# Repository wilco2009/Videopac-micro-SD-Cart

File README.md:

# Videopac µSD cart 
**©2020 Alejandro Valero (Wilco2009)**

Special thanks to Rene Van Den Enden

## INTRODUCTION
The Videopac µSD cart is a revolutionary cartridge allows the loading of Videopac/Magnavox Oddysey2 ROMs from a micro-SD card directly to the console.

Features:
-	Supports the Magnavox Oddysey2, Philips Videopac G7000, Videopac+ G7400, JOPAC and all compatible consoles
-	File selection with OLED display and/or ‘on screen’ game selector
- Supports the following ROM types:
   -	Standard P10/P11 games: 2K, 4K and 8K
   -	XROM games: Game 31 (Musician) & Game 40 (4 In Row)
   -	Videopac+ games: Game 55+ (12K), 58+, 59+ and 60+ (16K)
   -	Soren Gust format: 12K
-	Serial transfer from PC for developers
-	Hexadecimal memory monitor for debugging
-	USB upgradable firmware

## PREREQUISITES
The following items are required for a working system with the Videopac µSD cart:
1.	A Magnavox Oddysey2, Philips Videopac G7000, Videopac+ G7400, JOPAC etc. console
2.	The Videopac µSD cart itself
3.	A micro-SD card (not supplied)
4.	A copy of the “SD.ZIP” file containing the files for the Videopac µSD cart
 
## LAYOUT
The **Videopac µSD cart** connectors and elements are listed below:

## PREPARING THE SD CARD
The **Videopac µSD cart** supports any micro-SD card capacity formatted as FAT16 or FAT32.

The card must fully support the SPI communication protocol – there is a lot of variance in SD cards so for best results please use ‘known brand’ cards and if one card doesn’t work as expected then try another.

Preparing the SD card for the **Videopac µSD cart** is simple:

-	Card must be formatted in FAT16 or FAT32 format
-	The "GAMELIST.INI" file (see below) must be in the root directory of the card
-	A directory called “SYS” must be in the root directory
-	The master skeleton copy of the on-screen game selector ROM "SELECTGAME.BIN" must be in the “SYS” directory

A ZIP file “SD.ZIP” is supplied with the minimum structure required on the card which can be unzipped directly to the root of a freshly formatted SD card.

**Note:** Do not copy any other "SELECTGAME.BIN" into “SYS” other than the master one supplied.

## COPYING ROM FILES
When copying ROM files onto the Videopac µSD cart be aware that the on-screen game selector cannot currently navigate directories. Directories can be used for holding ROM files but will need to be selected using the OLED display and buttons before the game selector runs.

It is recommended that you place all ROM files in the root directory of the card for ease of use of the game selector.

**Note:** This restriction does not apply when directly selecting games using the OLED display and buttons.

## GAMELIST.INI
This file is supplied with the Videopac µSD cart and already contains entries for all the known games for the Videopac/Magnavox Odyssey2 platform, but is editable to make changes or add new entries if required.

The file is laid out in typical Windows INI file format where section names in square brackets correspond to the CRC32  value of a game file and beneath them the characteristics of the game.

An example for a complete game would be the following:

>[4EDA4917]
>
>NAME=01 Speedway! / Spin-Out! / Crypto-Logic!

>YEAR=1978
>
>MANUF=North American Philips Consumer Electronics Corp.
>
>VARIANT=Euro
>
>PAGGING=P10/P11

These values are read and used by the OLED display to show which game is running, the value "PAGGING" is used internally by the Videopac µSD cart to know how to manage the game's memory paging mode and can be set for P10/P11, VPPLUS, SOREN or XROM.

## SELECTGAME.BIN
This is the code for the on-screen file selector menu, use the joystick up and down and fire to select the file to load and once loaded, press ”RESET” key on the console to start.

**Note:** You cannot navigate directories at the current time.

Due to the way the console interacts with the **Videopac µSD cart**, a copy of the skeleton selection code from the “SYS” directory must be copied into the current directory and populated with the files it needs to show in this location, this is done when activating the “VPMENU” option.

The menu allows a maximum of 200 files at any one time, if there are more than this then moving left or right with the joystick will select the next group of 200 files.

When changing file group to get the next set of 200 files a new copy of “SELECTGAME.BIN” containing these files must be loaded, this is then activated by pressing the ”RESET” key on the console again.

Once a game is loaded pressing ”RESET” key on the console will restart the game, to return back to the menu, select “VPMENU” on the **Videopac µSD cart** and the menu will reload.

## MAIN MENU

Once the console is started with the **Videopac µSD cart** inserted it will boot and the OLED display will show the main menu options, use Direction buttons/Enter to select:

**OPTIONS:** “LOAD”, “VPMENU”, “CONFIG”, “RECEIVE”, “ABOUT” and “GAME”

### LOAD

This allows the selection of a .BIN file from the contents on the card to load into the **Videopac µSD cart*’s RAM memory using the buttons and the OLED display.
To select the file:

>-	“UP” & “DOWN” go back and forward one file
>-	“LEFT” & “RIGHT” go back and forward 20 files
>-	“ENTER” load the selected file into the memory or enter a sub directory
>-	“ESC” to go to the “FILE” sub-menu

Once the file is loaded into RAM memory with “ENTER”, press the "RESET" key on the console and follow the instructions for the corresponding game.

Pressing the “ESC” button on an item opens the "FILE" sub-menu which will gives access to the following options:

OPTIONS: “INFO”, “MONITOR” and “EXIT”

>-	INFO: Shows the information for the file and the corresponding metadata from “GAMESLIST.INI” if the CRC32 is known
>-	MONITOR: Displays the contents of the RAM memory in hexadecimal

>**Note:** Examining the RAM contents will decouple it from the running host console and will most likely not return without crashing.  When returning from this mode simply press "RESET" on the console to restore the game
>•	EXIT: Return to main menu
 
### VPMENU
Selecting this option will quit the current game and build the on-screen file selector code by making a copy of the skeleton “SELECTGAME.BIN” file in the current directory (as defined in the “LOAD” menu using the buttons and the OLED display) and populating it with the filenames from the current directory. Press the “RESET” button on the console to show the selection menu.

### CONFIG
OPTIONS: “SETDIR”, “AUTLOAD”, “LOGO”, “REBUILD”, “BAUD”, SORTED”
-	SETDIR: Assign the current directory as the directory from where the “SELECTGAME.BIN” will be read if “AUTOLOAD” is set (usually the root)
-	AUTOLOAD: Enables / disables automatic loading of the “SELECTGAME.BIN” file at start-up from the location defined by “SETDIR”
-	LOGO: Activates / deactivates the logo display during start-up
-	REBUILD: The "GAMELIST.INI" file and each directories file information are compiled and cached as binary index files to speed up file access and game information. This means that after changing the "GAMELIST.INI" file or add/removing files the indexes must be rebuilt:
   -	REBUILD GAMELIST: Generates game index file from the “GAMELIST.INI” file 
   -	REBUILD DIRECTORY: Generates file index files of the ROMs contained in the current directory
   -	WHEN: Choose when to perform rebuilding of the file indexes:
       - “ALWAYS”: The directory index is regenerated each time a directory is accessed with no need to regenerate the indexes each time a new ROM is added, but it will take longer to navigate and select a game
       - “MANUALLY”: The directory index files are not regenerated automatically and require manual rebuilding upon changes
- 	BAUD: Allows selection of the transmission speed of the serial port, valid values are: 
   -	9600 bps
   -	19200 bps
   -	38400 bps
   -	57600 bps
   -	115200 bps
-	SORTED: Select “YES” so that the files will appear sorted in alphabetical order
 
### RECEIVE
This is mainly aimed at developers and allows the connection of a PC to the **Videopac µSD cart** through an RS-232 serial connection (such as that supplied by a USB Serial Adaptor or Dongle) to load a program file directly into the RAM of the **Videopac µSD cart**.

The **Videopac µSD cart** serial connector header has the following pinout:

-	3 TX (Connect to the RX pin)
-	2 RX (Connect to the TX pin)
-	1 GND (Connect to the GND pin)

From the **Videopac µSD cart** side, select the desired data transmission speed (“BAUD”) in the “CONFIG” menu and select the “RECEIVE” option, transmission of the file from the PC can then begin.
From the PC side use the “UPLOAD.BAT file”, supplied in the “FLASH&SERIAL.ZIP” file that comes with the **Videopac µSD cart** to transfer the file.
The syntax for “UPLOAD.BAT” file is as follows:

> upload.bat <file.bin> [COMPORT] [BAUDRATE] [PAGGING]
> Where:
> -	COMPORT = COMport
> -	BAUDRATE = 9600, 19200(default), 38400, 56700, 115200
> -	PAGGING = P10/P11, VPPLUS, SOREN, XROM
For example, to load the file "VP01.BIN" at 115200 baud through the COM7 port, select the "RECEIVE" option on the **Videopac µSD cart** and then execute the following command on the PC:
> UPLOAD VP01.BIN COM7 115200 P10/P11
Once completed the transferred program can be executed by pressing “RESET” on the console in the usual way.

### ABOUT
Displays details about the **Videopac µSD cart** and the current version.
 
### GAME
This “easter egg” option allows you to play Videopac games using the OLED Display and direction buttons directly on the **Videopac µSD cart**, firmware V1.04 includes “Race” and “Pong.
To play, remove the **Videopac µSD cart** from the unit and attach the Arduino micro-USB port to a power source to before selecting this option followed by the required game.

When in-game pressing “ESC” will bring up a menu allowing sound to be disabled or the current game to quit and return to start.

To exit game you must remove power from the Arduino micro-USB port.
**Note:** Using the digital direction buttons will result in very different gameplay from using the analogue joysticks – good luck!

## UPDATING THE FIRMWARE
Updating the **Videopac µSD cart** with a new firmware version is as simple as connecting it with a micro-USB cable to a PC and executing a simple command.

Remove the **Videopac µSD cart** from the console and connect the Arduino micro-USB port to the PC, the Arduino driver should install and appear as a new CH340 COM port in the system.

The number of the COM port needs to be known and this can be determined by looking in the "Bluetooth and other devices" window of the Control Panel similar to this:

If there are problems finding the correct number of the port then there is a utility called "LISTCOM.EXE" supplied in the ZIP file that will list all the COM ports available on the PC, test each of these to find the correct port.

Once the port is known proceed to run the flashing utility “VPFLASH.BAT” supplied in the “FLASH&SERIAL.ZIP” ZIP file, having already copied the required ".HEX" firmware file to the same directory as the utility.

Depending on the OLED type on your **Videopac µSD cart** you will need to select the firmware for either the “blue screen” SH1106” or the “white screen” SSD1306.
The syntax of the utility is as follows:

> VPFLASH \[COMPORT\] \<file\>

For example, to load the file "update.HEX" through the COM7 port, execute the following command on the PC:

> VPFLASH COM7 update.HEX

**Note:** DO NOT INTERRUPT THE FLASHING PROCEDURE - Wait for the flashing operation to finish, after which the **Videopac µSD cart** will automatically reset.

## RESTORING FACTORY SETTINGS
To restore the **Videopac µSD cart**’s factory settings, hold both “ENTER”+”ESC” buttons while booting. This option can be used to restore defaults or after installing firmware for the first time.

## BOOTING WITHOUT DISPLAY
If you have any kind of problem with the OLED display it is still possible to use the **Videopac µSD cart** as long as there is a copy of "SELECTGAME.BIN" in the root folder.

By holding the buttons “ESC” + “LEFT” while booting, the **Videopac µSD cart** will automatically go into “VPMENU” mode allowing on-screen game selection with the joystick.

## DIAGNOSTICS
The **Videopac µSD cart** provides a diagnostic utility to output to a serial console in case of any issues.
To access diagnostics, disconnect the **Videopac µSD cart** from the console and connect to a computer with the USB cable from the Arduino micro-USB port.
Open a serial terminal  to the CH340 COM port described above with settings 9600bps, 8bits, no parity, 1 stop bit (9600/8/none/1).
Press “ENTER” + “LEFT” during start-up to access the diagnostic utility via the serial terminal.

## PROGRAMING THE CPLD
Updating the CPLD programming should not normally be required, but it may be necessary to update if a bug is found or some new functionality related to communication with the console is required.
Programming the CPLD requires a XILINX programming cable connected to the JTAG port header of the **Videopac µSD cart**.
It is beyond the scope of this manual to explain updating the CPLD via JTAG, but in the event of a CPLD release further guidance will be given with the update.

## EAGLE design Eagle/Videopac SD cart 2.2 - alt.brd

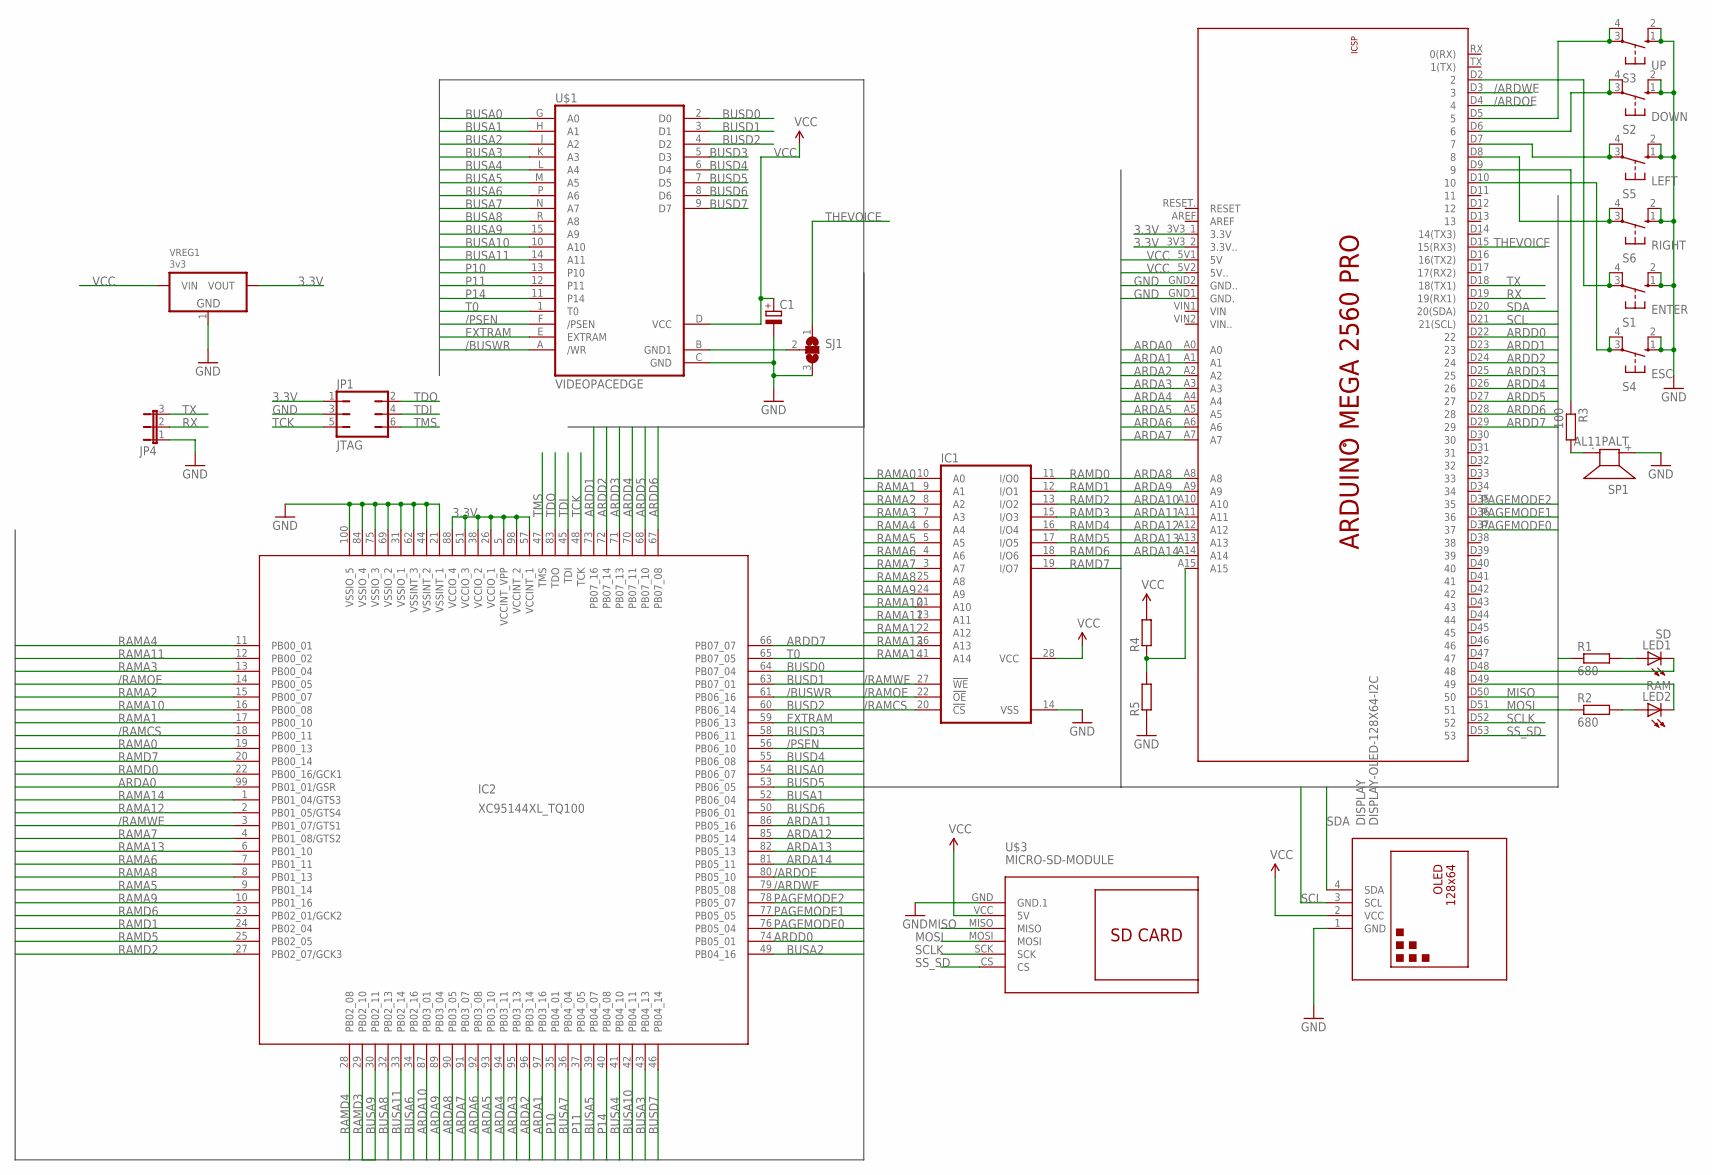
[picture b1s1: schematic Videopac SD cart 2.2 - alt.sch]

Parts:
C1: CPOL-EUE3.5-8; E3,5-8
DISPLAY: DISPLAY-OLED-128X64-I2C
IC1: 62256FPSOP28; SOP28
IC2: XC95144XL_TQ100; XC-TQ100
JP1: JTAG; JP3Q
JP4: JP2E; JP2
LED1: SD; LED3MM
LED2: RAM; LED3MM
R1, R2: 680; 0204/7
R3: 100; 0204/7
R4, R5: R-EU_0204/7; 0204/7
S1: ENTER; B3F-10XX
S2: DOWN; B3F-10XX
S3: UP; B3F-10XX
S4: ESC; B3F-10XX
S5: LEFT; B3F-10XX
S6: RIGHT; B3F-10XX
SJ1: SJ2W; SJ_2
SP1: AL11PALT; ALT
U$1: VIDEOPACEDGE; VIDEOPAC
U$2: ARDUINO_MEGA2560_PRO
U$3: MICRO-SD-MODULE; MICROSD-MODULE
VREG1: 3v3; SOT223

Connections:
3.3V: IC2.5 (VCCINT_VPP), IC2.26 (VCCIO_1), IC2.38 (VCCIO_2), IC2.51 (VCCIO_3), IC2.57 (VCCINT_1), IC2.88 (VCCIO_4), IC2.98 (VCCINT_2), JP1.1, U$2.3V3_1 (3.3V), U$2.3V3_2 (3.3V..), VREG1.2 (VOUT)
/ARDOE: IC2.80 (PB05_10), U$2.D4 (4)
/ARDWE: IC2.79 (PB05_08), U$2.D3 (3)
/BUSWR: IC2.61 (PB06_16), U$1.A (/WR)
/PSEN: IC2.56 (PB06_10), U$1.F (/PSEN)
/RAMCS: IC1.20 (!CS), IC2.18 (PB00_11)
/RAMOE: IC1.22 (!OE), IC2.14 (PB00_05)
/RAMWE: IC1.27 (!WE), IC2.3 (PB01_07/GTS1)
ARDA0: IC2.99 (PB01_01/GSR), U$2.A0
ARDA1: IC2.97 (PB03_16), U$2.A1
ARDA2: IC2.96 (PB03_14), U$2.A2
ARDA3: IC2.95 (PB03_13), U$2.A3
ARDA4: IC2.94 (PB03_11), U$2.A4
ARDA5: IC2.93 (PB03_10), U$2.A5
ARDA6: IC2.92 (PB03_08), U$2.A6
ARDA7: IC2.91 (PB03_07), U$2.A7
ARDA8: IC2.90 (PB03_05), U$2.A8
ARDA9: IC2.89 (PB03_04), U$2.A9
ARDA10: IC2.87 (PB03_01), U$2.A10
ARDA11: IC2.86 (PB05_16), U$2.A11
ARDA12: IC2.85 (PB05_14), U$2.A12
ARDA13: IC2.82 (PB05_13), U$2.A13
ARDA14: IC2.81 (PB05_11), U$2.A14
ARDD0: IC2.74 (PB05_01), U$2.D22 (22)
ARDD1: IC2.73 (PB07_16), U$2.D23 (23)
ARDD2: IC2.72 (PB07_14), U$2.D24 (24)
ARDD3: IC2.71 (PB07_13), U$2.D25 (25)
ARDD4: IC2.70 (PB07_11), U$2.D26 (26)
ARDD5: IC2.68 (PB07_10), U$2.D27 (27)
ARDD6: IC2.67 (PB07_08), U$2.D28 (28)
ARDD7: IC2.66 (PB07_07), U$2.D29 (29)
BUSA0: IC2.54 (PB06_07), U$1.G (A0)
BUSA1: IC2.52 (PB06_04), U$1.H (A1)
BUSA2: IC2.49 (PB04_16), U$1.J (A2)
BUSA3: IC2.43 (PB04_13), U$1.K (A3)
BUSA4: IC2.41 (PB04_10), U$1.L (A4)
BUSA5: IC2.39 (PB04_07), U$1.M (A5)
BUSA6: IC2.34 (PB02_16), U$1.P (A6)
BUSA7: IC2.36 (PB04_04), U$1.N (A7)
BUSA8: IC2.32 (PB02_13), U$1.R (A8)
BUSA9: IC2.30 (PB02_11), U$1.15 (A9)
BUSA10: IC2.42 (PB04_11), U$1.10 (A10)
BUSA11: IC2.33 (PB02_14), U$1.14 (A11)
BUSD0: IC2.64 (PB07_04), U$1.2 (D0)
BUSD1: IC2.63 (PB07_01), U$1.3 (D1)
BUSD2: IC2.60 (PB06_14), U$1.4 (D2)
BUSD3: IC2.58 (PB06_11), U$1.5 (D3)
BUSD4: IC2.55 (PB06_08), U$1.6 (D4)
BUSD5: IC2.53 (PB06_05), U$1.7 (D5)
BUSD6: IC2.50 (PB06_01), U$1.8 (D6)
BUSD7: IC2.46 (PB04_14), U$1.9 (D7)
BUTTON_A: S4.3, S4.4 (P1), U$2.D10 (10)
BUTTON_B: S1.3, S1.4 (P1), U$2.D2 (2)
BUTTON_DOWN: S2.3, S2.4 (P1), U$2.D6 (6)
BUTTON_LEFT: S5.3, S5.4 (P1), U$2.D7 (7)
BUTTON_RIGHT: S6.3, S6.4 (P1), U$2.D8 (8)
BUTTON_UP: S3.3, S3.4 (P1), U$2.D5 (5)
EXTRAM: IC2.59 (PB06_13), U$1.E (EXTRAM)
GND: C1.-, DISPLAY.1 (GND), IC1.14 (VSS), IC2.21 (VSSINT_1), IC2.31 (VSSIO_1), IC2.44 (VSSINT_2), IC2.62 (VSSINT_3), IC2.69 (VSSIO_2), IC2.75 (VSSIO_3), IC2.84 (VSSIO_4), IC2.100 (VSSIO_5), JP1.3, JP4.1, R5.1, S1.1 (S), S1.2 (S1), S2.1 (S), S2.2 (S1), S3.1 (S), S3.2 (S1), S4.1 (S), S4.2 (S1), S5.1 (S), S5.2 (S1), S6.1 (S), S6.2 (S1), SJ1.3, SP1.+ (1), U$1.C (GND), U$2.GND1 (GND.), U$2.GND2 (GND..), U$3.GND (GND.1), VREG1.1 (GND)
MISO: U$2.D50 (50), U$3.MISO
MOSI: U$2.D51 (51), U$3.MOSI
unnamed: LED1.A, R1.2
unnamed: LED2.A, R2.2
unnamed: LED1.K (C), U$2.D48 (48)
unnamed: LED2.K (C), U$2.D49 (49)
unnamed: R3.1, U$2.D9 (9)
unnamed: SJ1.2, U$1.B (GND1)
unnamed: R4.1, R5.2, U$2.A15
unnamed: R3.2, SP1.- (2)
P10: IC2.35 (PB04_01), U$1.13 (P10)
P11: IC2.37 (PB04_05), U$1.12 (P11)
P14: IC2.40 (PB04_08), U$1.11 (P14)
PAGEMODE0: IC2.76 (PB05_04), U$2.D37 (37)
PAGEMODE1: IC2.77 (PB05_05), U$2.D36 (36)
PAGEMODE2: IC2.78 (PB05_07), U$2.D35 (35)
RAMA0: IC1.10 (A0), IC2.19 (PB00_13)
RAMA1: IC1.9 (A1), IC2.17 (PB00_10)
RAMA2: IC1.8 (A2), IC2.15 (PB00_07)
RAMA3: IC1.7 (A3), IC2.13 (PB00_04)
RAMA4: IC1.6 (A4), IC2.11 (PB00_01)
RAMA5: IC1.5 (A5), IC2.9 (PB01_14)
RAMA6: IC1.4 (A6), IC2.7 (PB01_11)
RAMA7: IC1.3 (A7), IC2.4 (PB01_08/GTS2)
RAMA8: IC1.25 (A8), IC2.8 (PB01_13)
RAMA9: IC1.24 (A9), IC2.10 (PB01_16)
RAMA10: IC1.21 (A10), IC2.16 (PB00_08)
RAMA11: IC1.23 (A11), IC2.12 (PB00_02)
RAMA12: IC1.2 (A12), IC2.2 (PB01_05/GTS4)
RAMA13: IC1.26 (A13), IC2.6 (PB01_10)
RAMA14: IC1.1 (A14), IC2.1 (PB01_04/GTS3)
RAMD0: IC1.11 (I/O0), IC2.22 (PB00_16/GCK1)
RAMD1: IC1.12 (I/O1), IC2.24 (PB02_04)
RAMD2: IC1.13 (I/O2), IC2.27 (PB02_07/GCK3)
RAMD3: IC1.15 (I/O3), IC2.29 (PB02_10)
RAMD4: IC1.16 (I/O4), IC2.28 (PB02_08)
RAMD5: IC1.17 (I/O5), IC2.25 (PB02_05)
RAMD6: IC1.18 (I/O6), IC2.23 (PB02_01/GCK2)
RAMD7: IC1.19 (I/O7), IC2.20 (PB00_14)
RX: JP4.2, U$2.D19 (19(RX1))
SCL: DISPLAY.3 (SCL), U$2.D21 (21(SCL))
SCLK: U$2.D52 (52), U$3.SCK
SDA: DISPLAY.4 (SDA), U$2.D20 (20(SDA))
SS_SD: U$2.D53 (53), U$3.CS
T0: IC2.65 (PB07_05), U$1.1 (T0)
TCK: IC2.48 (TCK), JP1.5
TDI: IC2.45 (TDI), JP1.4
TDO: IC2.83 (TDO), JP1.2
THEVOICE: SJ1.1, U$2.D15 (15(RX3))
TMS: IC2.47 (TMS), JP1.6
TX: JP4.3, U$2.D18 (18(TX1))
VCC: C1.+, DISPLAY.2 (VCC), IC1.28 (VCC), R1.1, R2.1, R4.2, U$1.D (VCC), U$2.5V1 (5V), U$2.5V2 (5V..), U$3.VCC (5V), VREG1.3 (VIN)

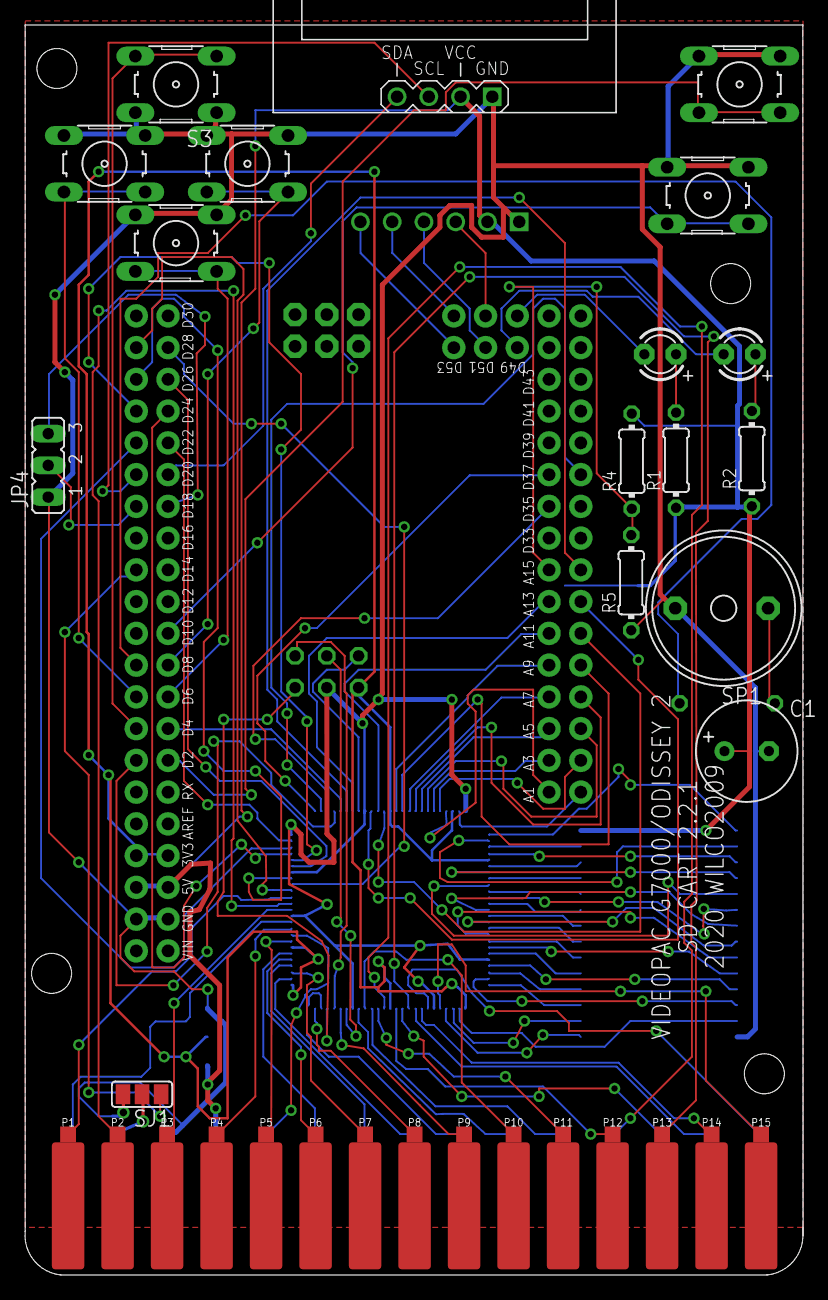
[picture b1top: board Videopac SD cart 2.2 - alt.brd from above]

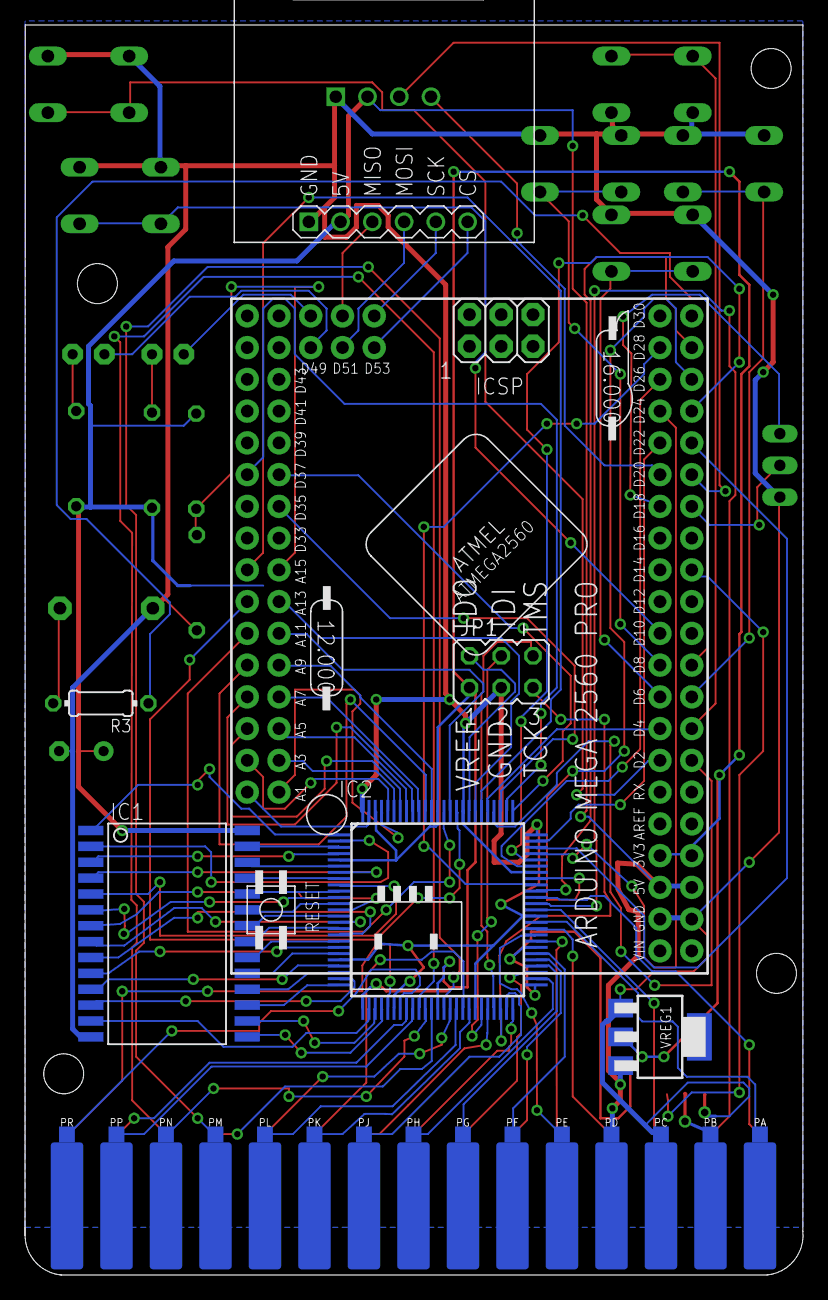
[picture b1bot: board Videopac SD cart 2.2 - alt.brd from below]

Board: 2 copper layers, 62.2 x 100.0 mm, 25 parts (7 on the bottom side), 111 nets.

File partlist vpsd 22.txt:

Part     Value                   Package

C1       100uF                   
DISPLAY  DISPLAY-OLED-128X64-I2C 
IC1      UT62256SLC              SOP28
IC2      XC95144XL_TQ100	     TQ100
LED1     SD                      LED3MM
LED2     RAM                     LED3MM
R1       680                     R-EU_0204/7
R2       680                     R-EU_0204/7
R3       100                     R-EU_0204/7
R4       NO INSTALAR             R-EU_0204/7
R5       NO INSTALAR             R-EU_0204/7
S1..A6   PUSH BUTTONS            Height = 11mm
SP1      BUZZER 5V               TMB12A05
U$2      ARDUINO_MEGA2560_PRO    
U$3      MICRO-SD-MODULE         
VREG1    AMS1117-3.3             SOT223

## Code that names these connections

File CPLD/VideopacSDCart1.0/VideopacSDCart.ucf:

#PACE: Start of Constraints generated by PACE

#PACE: Start of PACE I/O Pin Assignments

#PACE: Start of PACE Area Constraints

#PACE: Start of PACE Prohibit Constraints

#PACE: End of Constraints generated by PACE

NET "BUSD<0>"								PULLUP;
NET "BUSD<1>"								PULLUP;
NET "BUSD<2>"								PULLUP;
NET "BUSD<3>"								PULLUP;
NET "BUSD<4>"								PULLUP;
NET "BUSD<5>"								PULLUP;
NET "BUSD<6>"								PULLUP;
NET "BUSD<7>"								PULLUP;
NET "BUSA<10>"								PULLUP;
NET "P14"									PULLUP;
NET "P11"									PULLUP;
NET "P10"									PULLUP;
NET "BUSA<11>"								PULLUP;
NET "BUSA<9>"								PULLUP;

NET "RAMA<14>"								LOC =  "S:PIN1";
NET "RAMA<12>"								LOC =  "S:PIN2";
NET "RAMWE"									LOC =  "S:PIN3";
NET "RAMA<7>"								LOC =  "S:PIN4";
NET "RAMA<13>"								LOC =  "S:PIN6";
NET "RAMA<6>"								LOC =  "S:PIN7";
NET "RAMA<8>"								LOC =  "S:PIN8";
NET "RAMA<5>"								LOC =  "S:PIN9";
NET "RAMA<9>"								LOC =  "S:PIN10";
NET "RAMA<4>"								LOC =  "S:PIN11";
NET "RAMA<11>"								LOC =  "S:PIN12";
NET "RAMA<3>"								LOC =  "S:PIN13";
NET "RAMOE"									LOC =  "S:PIN14";
NET "RAMA<2>"								LOC =  "S:PIN15";
NET "RAMA<10>"								LOC =  "S:PIN16";
NET "RAMA<1>"								LOC =  "S:PIN17";
NET "RAMCS"									LOC =  "S:PIN18";
NET "RAMA<0>"								LOC =  "S:PIN19";
NET "RAMD<7>"								LOC =  "S:PIN20";
NET "RAMD<0>"								LOC =  "S:PIN22";
NET "RAMD<6>"								LOC =  "S:PIN23";
NET "RAMD<1>"								LOC =  "S:PIN24";
NET "RAMD<5>"								LOC =  "S:PIN25";
NET "RAMD<2>"								LOC =  "S:PIN27";
NET "RAMD<4>"								LOC =  "S:PIN28";
NET "RAMD<3>"								LOC =  "S:PIN29";
NET "BUSA<9>"								LOC =  "S:PIN30";
NET "BUSA<8>"								LOC =  "S:PIN32";
NET "BUSA<11>"								LOC =  "S:PIN33";
NET "BUSA<6>"								LOC =  "S:PIN34";
NET "P10"									LOC =  "S:PIN35";
NET "BUSA<7>"								LOC =  "S:PIN36";
NET "P11"									LOC =  "S:PIN37";
NET "BUSA<5>"								LOC =  "S:PIN39";
NET "P14"									LOC =  "S:PIN40";
NET "BUSA<4>"								LOC =  "S:PIN41";
NET "BUSA<10>"								LOC =  "S:PIN42";
NET "BUSA<3>"								LOC =  "S:PIN43";
NET "BUSD<7>"								LOC =  "S:PIN46";
NET "BUSA<2>"								LOC =  "S:PIN49";
NET "BUSD<6>"								LOC =  "S:PIN50";
NET "BUSA<1>"								LOC =  "S:PIN52";
NET "BUSD<5>"								LOC =  "S:PIN53";
NET "BUSA<0>"								LOC =  "S:PIN54";
NET "BUSD<4>"								LOC =  "S:PIN55";
NET "PSEN"									LOC =  "S:PIN56";
NET "BUSD<3>"								LOC =  "S:PIN58";
NET "EXTRAM"								LOC =  "S:PIN59";
NET "BUSD<2>"								LOC =  "S:PIN60";
NET "BUSWR"									LOC =  "S:PIN61";
NET "BUSD<1>"								LOC =  "S:PIN63";
NET "BUSD<0>"								LOC =  "S:PIN64";
NET "T0"										LOC =  "S:PIN65";
NET "ARDD<7>"								LOC =  "S:PIN66";
NET "ARDD<6>"								LOC =  "S:PIN67";
NET "ARDD<5>"								LOC =  "S:PIN68";
NET "ARDD<4>"								LOC =  "S:PIN70";
NET "ARDD<3>"								LOC =  "S:PIN71";
NET "ARDD<2>"								LOC =  "S:PIN72";
NET "ARDD<1>"								LOC =  "S:PIN73";
NET "ARDD<0>"								LOC =  "S:PIN74";
NET "PAGEMODE<0>"							LOC =  "S:PIN76";
NET "PAGEMODE<1>"							LOC =  "S:PIN77";
NET "PAGEMODE<2>"							LOC =  "S:PIN78";
NET "ARDWE"									LOC =  "S:PIN79";
NET "ARDOE"									LOC =  "S:PIN80";
NET "ARDA<14>"								LOC =  "S:PIN81";
NET "ARDA<13>"								LOC =  "S:PIN82";
NET "ARDA<12>"								LOC =  "S:PIN85";
NET "ARDA<11>"								LOC =  "S:PIN86";
NET "ARDA<10>"								LOC =  "S:PIN87";
NET "ARDA<9>"								LOC =  "S:PIN89";
NET "ARDA<8>"								LOC =  "S:PIN90";
NET "ARDA<7>"								LOC =  "S:PIN91";
NET "ARDA<6>"								LOC =  "S:PIN92";
NET "ARDA<5>"								LOC =  "S:PIN93";
NET "ARDA<4>"								LOC =  "S:PIN94";
NET "ARDA<3>"								LOC =  "S:PIN95";
NET "ARDA<2>"								LOC =  "S:PIN96";
NET "ARDA<1>"								LOC =  "S:PIN97";
NET "ARDA<0>"								LOC =  "S:PIN99";

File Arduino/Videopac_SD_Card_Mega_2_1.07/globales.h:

#define SDFAT
#ifdef SH1106
U8G2_SH1106_128X64_NONAME_F_HW_I2C u8g2(U8G2_R2, /* reset=*/ U8X8_PIN_NONE);
char disp[]="SH1106";
#endif
#ifdef SSD1306
U8G2_SSD1306_128X64_NONAME_F_HW_I2C u8g2(U8G2_R2, /* reset=*/ U8X8_PIN_NONE);
char disp[]="SSD1306";
#endif

char str_GAMEOVER[] = "GAME OVER";

#define BLOCK_SIZE 256

#define PAG_P10_P11       0
#define PAG_VP_PLUS       1
#define PAG_SOREN         2
#define PAG_SELECT_GAME   3
#define PAG_TEST          4
#define PAG_XROM          5
#define MODE_PLAYING      0
#define MODE_SENDING_GAME 1

#define DIR_TO_BUS LOW
#define DIR_TO_CART HIGH
#define DISABLE_BUFFER HIGH 
#define ENABLE_BUFFER LOW 
#define MAX_FILENAME_LEN 100
#define MAX_DIRNAME_LEN 100
#define MAX_DEPTH 5
#define MAXDIR 200

#define GAME_NAME_LEN 101
#define GAME_BRAND_LEN 101
#define GAME_YEAR_LEN 21
#define GAME_VARIANT_LEN 51


  const int SPEAKER_PIN = 9;
  const int VOICE_PIN = 46;
  const int WR        = 3;
  const int OE        = 4;

  const int butUP     = 5;
  const int butDOWN   = 6;
  const int butLEFT   = 7;
  const int butRIGHT  = 8;
  const int butENTER  = 2;
  const int butESC    = 10;
  const int THEVOICE_SELECT_PIN = 11;


  const int PAGEMODE0 = 37;
  const int PAGEMODE1 = 36;
  const int PAGEMODE2 = 35;

  const int LED_SD    = 48;
  const int LED_RAM   = 49;
  

  const int pMISO      = 50;
  const int pMOSI      = 51;
  const int pSCK       = 52;
  const int pSPICS     = 53;

// byte pagging = PAG_P10_P11;

//TMRpcm tmrpcm;   // create an object for use in this sketch

boolean showVolt = false;

byte TheVoice = 0;

boolean resetting = false;

boolean SDOK = false;

boolean sorted = true;

boolean autorebuild = true;

boolean minigame_sound = true;

byte remotepgm = 0;
unsigned int cont;
unsigned int direccion = 0;
byte block[BLOCK_SIZE+1];
char str1[MAX_FILENAME_LEN];
char str2[MAX_FILENAME_LEN];
//char str3[MAX_FILENAME_LEN];
char file_name[MAX_FILENAME_LEN] = "vp_01.bin";
char file_loaded[MAX_FILENAME_LEN] = "";
char autoload_file[MAX_FILENAME_LEN] = "SELECTGAME.BIN";
char dir_name[MAXDIR] = "/";
char initial_dir[MAXDIR] = "/";
char strVER[]="1.07";
char strCacheFName[] = "$$$$$$$$.$$$";

char msgSDNOTOK[] = "uSD card not found";

bool to_show_logo = true;

char game_name[GAME_NAME_LEN] = "";
char game_brand[GAME_BRAND_LEN] = "";
char game_year[GAME_YEAR_LEN] = "";
char game_variant[GAME_VARIANT_LEN] = "";
byte game_pagging = 0;
int game_size = 0;
int game_BANK = 0;

unsigned long int bauds[] = {9600, 19200, 38400, 57600, 115200};

boolean show_descrition = true;
unsigned long int game_CRC = 0;
byte baudrate = 0;
int RAM_pos = 0;
byte RAM_delay;

int ch_ini;
static long int ti;

#ifdef SDFAT
SdFat sd;
SdFile file;
SdFile cache;
SdFile dirFile;


SdFile iniFile;
SdFile CRCFile;
SdFile dataFile;
SdFile descindex;
#else
File file;
File cache;
File dirFile;


File iniFile;
File CRCFile;
File dataFile;
File descindex;
#endif

int num_files = 0;
int num_files_nodir = 0;
long int inicio = 0;

//TMRpcm audio;   // create an object for use in this sketch

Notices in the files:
parts and their libraries:
diy-modules: Released under the Creative Commons Attribution 4.0 International License: http://creativecommons.org/licenses/by/4.0
SparkFun-Aesthetics: Licensing: Creative Commons ShareAlike 4.0 International - https://creativecommons.org/licenses/by-sa/4.0
